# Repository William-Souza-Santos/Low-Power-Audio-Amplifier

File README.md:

## Low-Power-Audio-Amplifier

#### Amplifier is electronic circuits that change input signal e amplifies the output signal
This hardware project is a very simple audio amplifier with basic components (LM358) was used the open source software of hardware development KiCAD to make this project

#### Main Component LM358: 

<div align="center">

</div>

## Schematic

IN_MIC is the audio signal input and OUT_MIC is the audio signal output

<div align="center">

</div>

## PCB Layout 

<div align="center">

</div>

## 3D View 

<div align="center">

</div>

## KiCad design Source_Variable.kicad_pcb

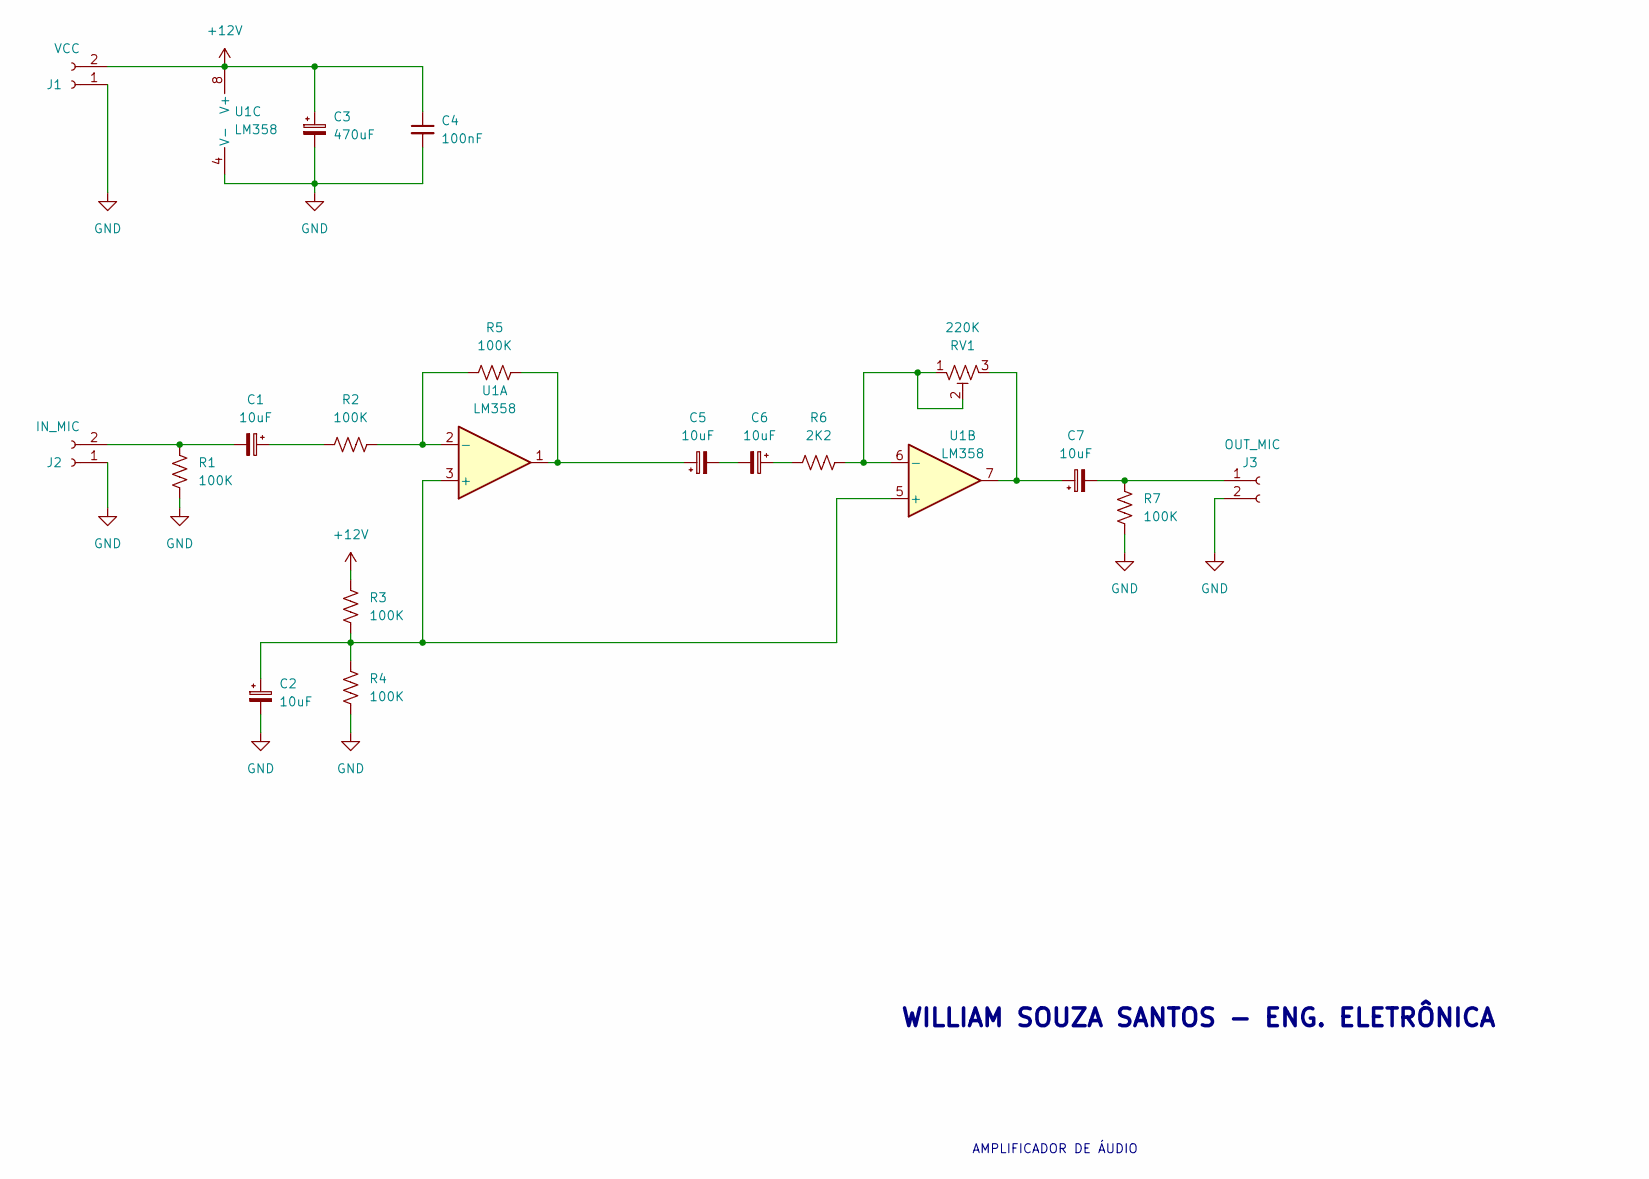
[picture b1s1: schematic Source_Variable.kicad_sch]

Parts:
C1, C2, C5, C6, C7: 10uF; CP_Radial_D8.0mm_P3.50mm
C3: 470uF; CP_Radial_D8.0mm_P3.50mm
C4: 100nF; C_Disc_D5.0mm_W2.5mm_P5.00mm
J1: VCC; TerminalBlock_bornier-2_P5.08mm
J2: IN_MIC; TerminalBlock_bornier-2_P5.08mm
J3: OUT_MIC; TerminalBlock_bornier-2_P5.08mm
R1, R2, R3, R4, R5, R7: 100K; R_Axial_DIN0207_L6.3mm_D2.5mm_P7.62mm_Horizontal
R6: 2K2; R_Axial_DIN0207_L6.3mm_D2.5mm_P7.62mm_Horizontal
RV1: 220K; Potentiometer_Bourns_3296W_Vertical
U1: LM358; DIP-8_W7.62mm_LongPads

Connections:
+12V: C3.1, C4.1, J1.2, R3.2, U1.8 (V+)
GND: C2.2, C3.2, C4.2, J1.1, J2.1, J3.2, R1.1, R4.1, R7.1, U1.4 (V-)
unnamed: C1.1, R2.1
unnamed: C1.2, J2.2, R1.2
unnamed: C2.1, R3.1, R4.2, U1.3 (+), U1.5 (+)
unnamed: C5.1, R5.2, U1.1
unnamed: C5.2, C6.2
unnamed: C6.1, R6.2
unnamed: C7.1, RV1.3, U1.7
unnamed: C7.2, J3.1, R7.2
unnamed: R2.2, R5.1, U1.2 (-)
unnamed: R6.1, RV1.1, RV1.2, U1.6 (-)

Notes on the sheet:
WILLIAM SOUZA SANTOS - ENG. ELETRÔNICA
AMPLIFICADOR DE ÁUDIO

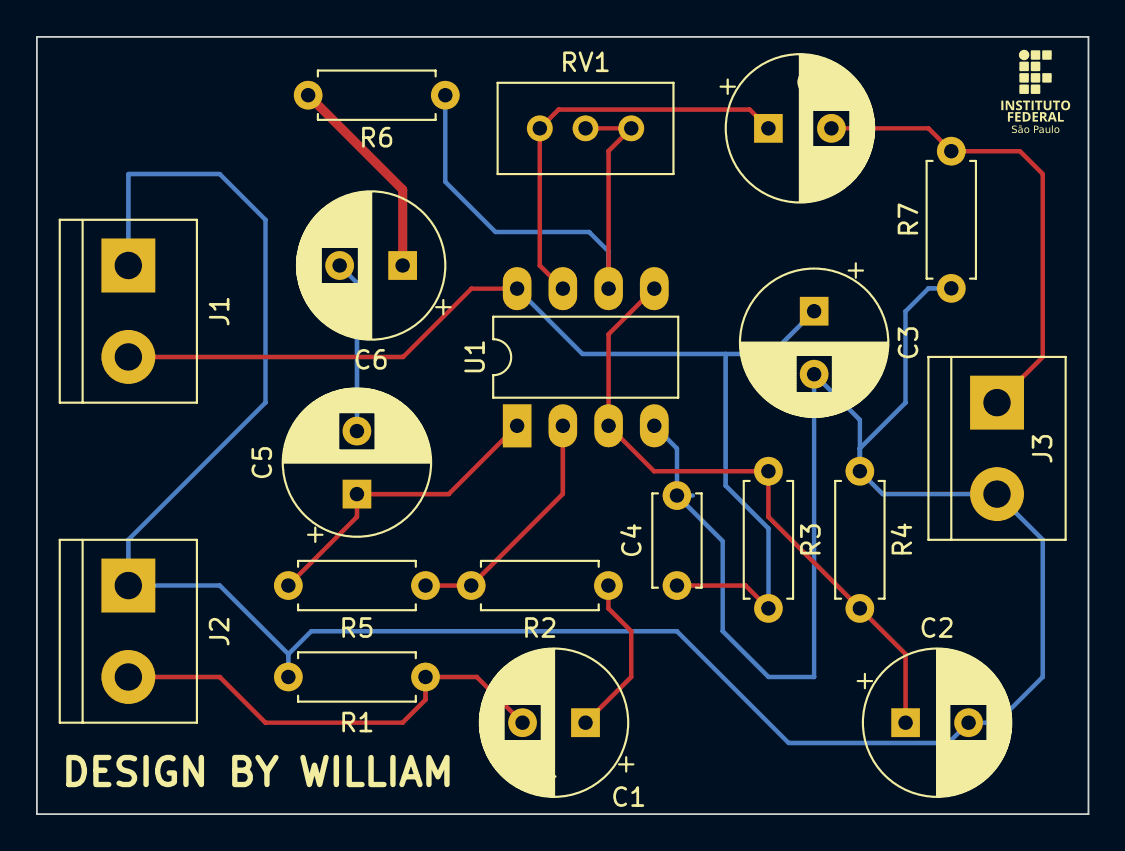
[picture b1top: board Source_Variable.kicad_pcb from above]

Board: 2 copper layers, 58.4 x 43.2 mm, 19 parts (0 on the bottom side), 12 nets.
